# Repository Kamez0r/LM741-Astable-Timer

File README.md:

# LM741-Astable-Timer
My university project for computer assisted design classes. I was assigned to design an astable timer using LM741.

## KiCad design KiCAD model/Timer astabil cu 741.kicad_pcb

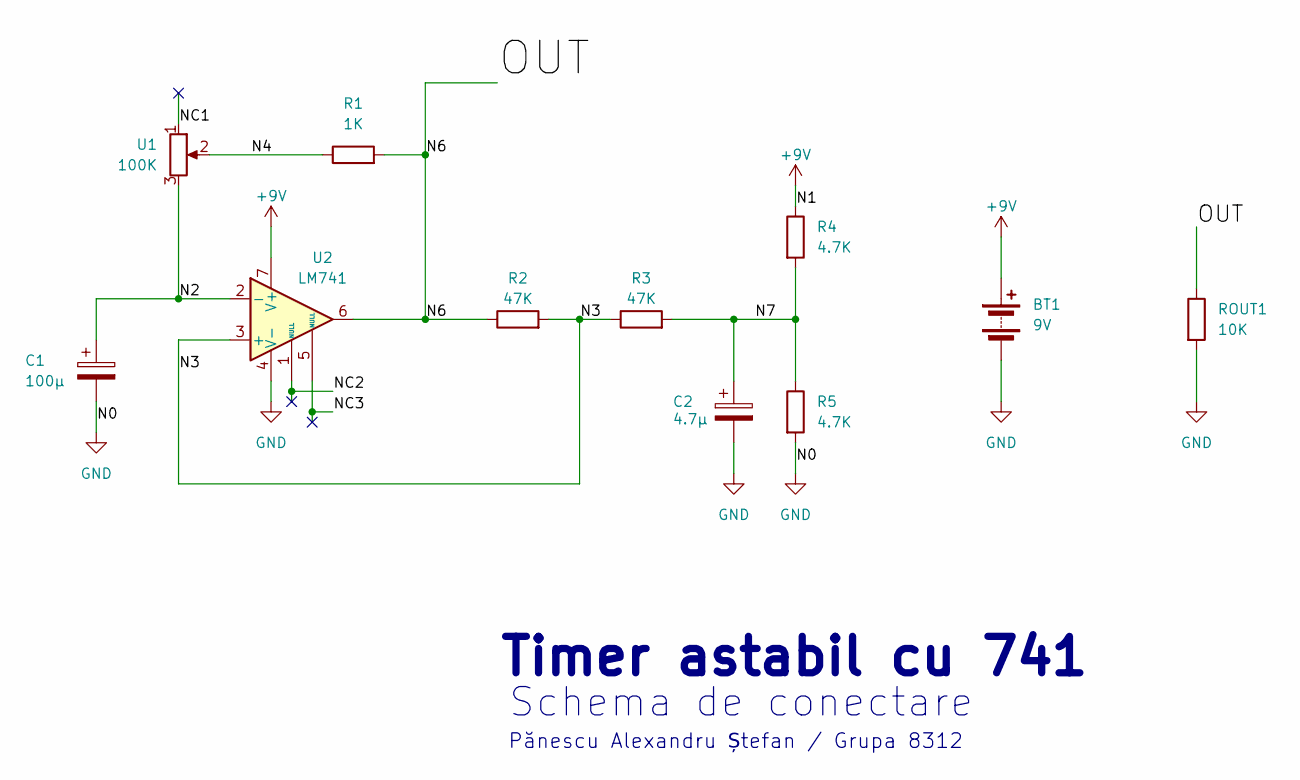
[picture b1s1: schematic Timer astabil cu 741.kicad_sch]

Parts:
BT1: 9V; BatteryHolder_MPD_BA9VPC_1xPP3
C1: 100μ; CP_Radial_D8.0mm_P3.50mm
C2: 4.7μ; CP_Radial_D5.0mm_P2.00mm
R1: 1K; R_Axial_DIN0411_L9.9mm_D3.6mm_P15.24mm_Horizontal
R2, R3: 47K; R_Axial_DIN0411_L9.9mm_D3.6mm_P15.24mm_Horizontal
R4, R5: 4.7K; R_Axial_DIN0411_L9.9mm_D3.6mm_P15.24mm_Horizontal
ROUT1: 10K; PinHeader_1x02_P1.27mm_Horizontal
U1: 100K; Potentiometer_Piher_PC-16_Single_Horizontal
U2: LM741; DIP-8_W7.62mm

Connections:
+9V: BT1.1 (+), R4.1, U2.7 (V+)
/N2: C1.1, U1.3, U2.2 (-)
/N3: R2.2, R3.1, U2.3 (+)
/N4: R1.1, U1.2
/N6: R1.2, R2.1, ROUT1.1, U2.6
/N7: C2.1, R3.2, R4.2, R5.1
/NC1: U1.1
/NC2: U2.1 (NULL)
/NC3: U2.5 (NULL)
GND: BT1.2 (-), C1.2, C2.2, R5.2, ROUT1.2, U2.4 (V-)

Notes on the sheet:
Schema de conectare
Pănescu Alexandru Ștefan / Grupa 8312
Timer astabil cu 741

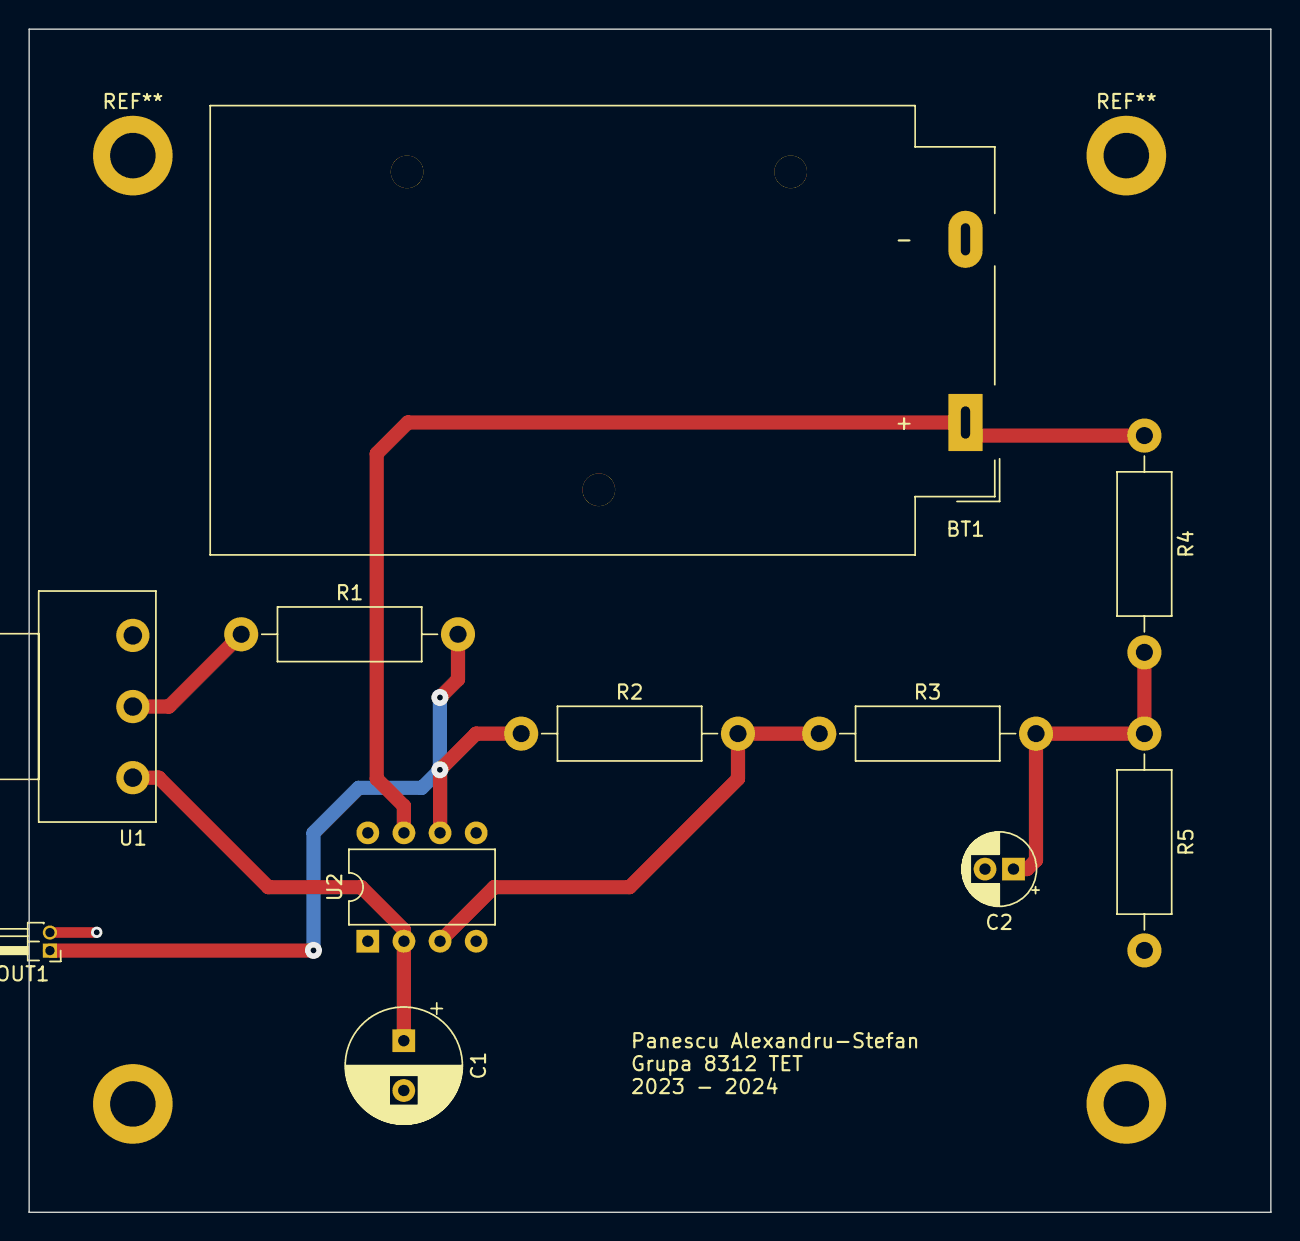
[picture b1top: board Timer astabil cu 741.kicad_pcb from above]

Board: 2 copper layers, 87.3 x 83.2 mm, 11 parts (0 on the bottom side), 7 nets.

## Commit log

2024-04-04 Main Paper
    Added main paper docx and pdf format that abstracts the whole project into several pages.
2024-04-04 Create README.md in annex
2024-04-04 SPICE .tran and .dc
    Added spice .tran and .dc analysis outputs plotted in pdf format
2024-04-04 KiCAD exports
    Added kicad exports - the kicad schematic, pcb front and back traces and edge cuts. a 3d render of the board.
2024-04-04 KiCAD project files
2024-04-04 LTSpice simulation files
    added network associated with the circuit and relevant libraries used
